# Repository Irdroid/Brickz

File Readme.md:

**Brickz Bluetooth Infrared Blaster / Transmitter by Irdroid**

**Introduction** 

Brickz is a Open Source Platform Independent Bluetooth Infrared Transmitter / Blaster that supports GNU Linux, MS Windows MAC OS X and Android. Brickz allows you to transmit Pronto HEX Infrared codes via its built-in infrared LEDs or via a IR extender cable that connect to brickz via a 3.5mm Mono Audio jack. The unit is capable of connecting to the host PC via USB as well as Bluetooth. It shows up as a bluetooth serial port, when that interface option is used, or as a USB Serial Device if the USB Interface connection is used.(https://irdroid.eu/product/brickz/)

**Features:**
- Bluetooth communication with the HOST SYSTEM / MCU
- USB Connection with the host System
- Built-in high power infrared leds
- Optional infrared transmitter extender
- Infrared operates at 940nm wavelength

**Example Application:**
- Digital signage infrared remote control & automation
- Home Automation & remote control
- Media remote control & automation systems

**How It works?**

Brickz listens for PRONTO HEX infrared codes via USB<>Serial or Bluetooht, simply connect to brickz via Bluetooth or USB open a terminal and type in the PRONTO code and hit enter, the command will be blasted through Brickz.If you are using Brickz with Android you can check out the example open source application that comes with brickz for sending pronto HEX codes. For detailed examples and usage, please refer to Brickz User's Manual, available in this repo.

On MAC OS X and GNU Linux once you pair with Brickz you can send PRONTO HEX codes directly from the console or via a bash script. This gives you the ability to make automation using script or controlling infrared devices directly from the console, from a script or scheduling infrared commands via cron. On MS Windows you can use any terminal application such as realterm or putty to send infrared commands with Brickz, or use the SerialSend.exe command line utility to send Infrared Codes to Brickz.

**Product website and Documentation**

- [Brickz official product Website](https://irdroid.eu/product/brickz)
- Documentation, Schematics, Production files and Software for Brickz can be found in this repository.

**Purchase sample unit**

- [Brickz official product Website](https://irdroid.eu/product/brickz)
- [Tindie](https://www.tindie.com/products/irdroid/brickz-bluetooth-infrared-transmitter/)

**You want to help with the development?**

- Write us an email to info@irdroid.com

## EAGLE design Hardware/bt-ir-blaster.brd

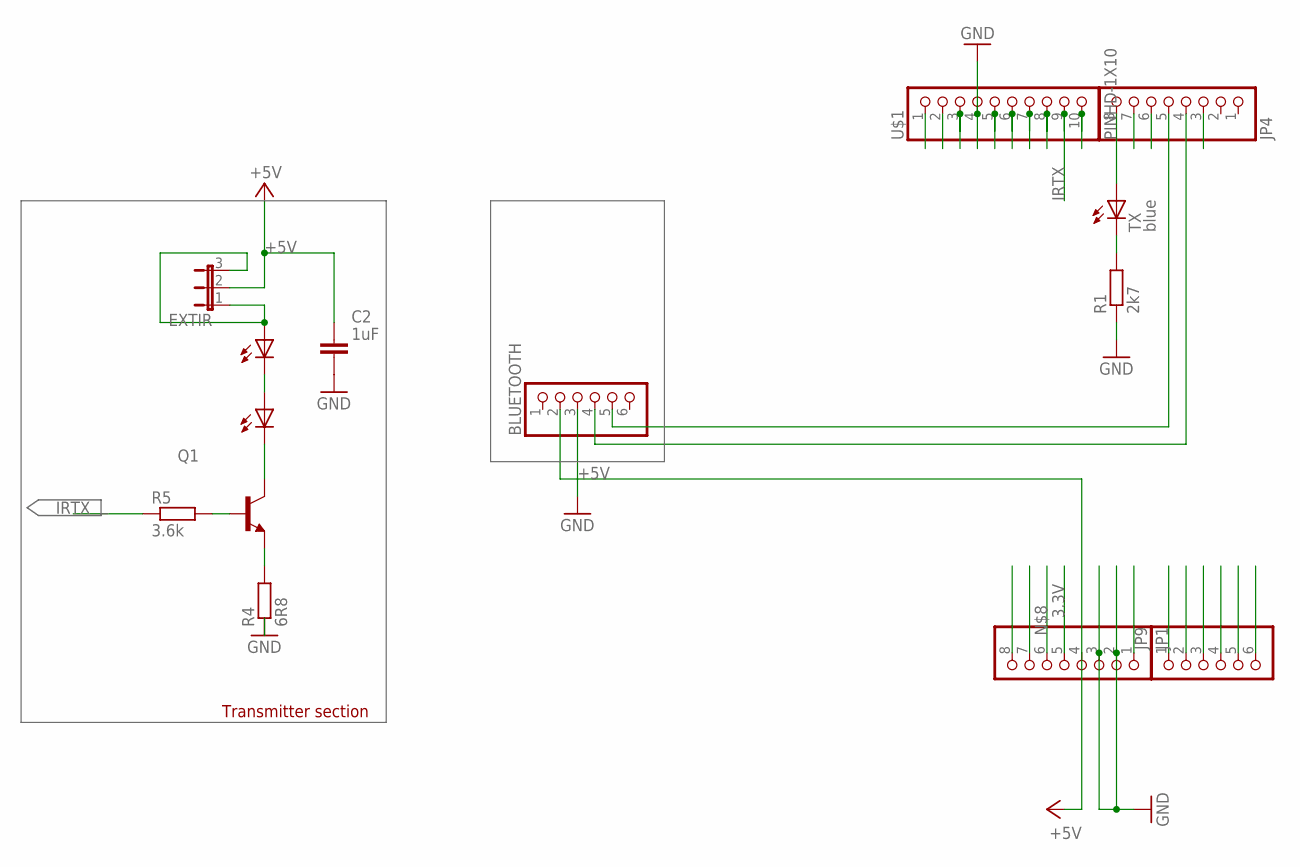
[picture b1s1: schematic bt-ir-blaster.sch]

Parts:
BLUETOOTH: PINHD-1X6; 1X06
C2: 1uF; C603@1
EXTIR: JP2E; JP2
JP1, JP4: PINHD-1X8BIG; 1X08-BIG
JP9: PINHD-1X6B; 1X06-BIG
Q1: TRANSISTOR_BJT_NPN-SOT-23-BCE; SOT-23
R1: 2k7; R0805
R4: 6R8; R1206
R5: 3.6k; R0603
TX: blue; LED3MM
U$1: PINHD-1X10; 1X10-BIG
U$5, U$7: IRLED5MM; IRLED_HOLDER

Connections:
3.3V: JP1.5
+5V: BLUETOOTH.2, C2.1, EXTIR.2, JP1.4
A: Q1.2 (C), U$5.K (C)
GND: BLUETOOTH.3, C2.2, JP1.2, JP1.3, R1.1, R4.1, U$1.4
IRTX: R5.1, U$1.9
K: Q1.3 (E), R4.2
unnamed: Q1.1 (B), R5.2
unnamed: U$5.A, U$7.K (C)
unnamed: R1.2, TX.K (C)
unnamed: EXTIR.1, EXTIR.3, U$7.A
unnamed: BLUETOOTH.4, JP4.4
unnamed: BLUETOOTH.5, JP4.5
unnamed: JP4.8, TX.A

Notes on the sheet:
Transmitter section

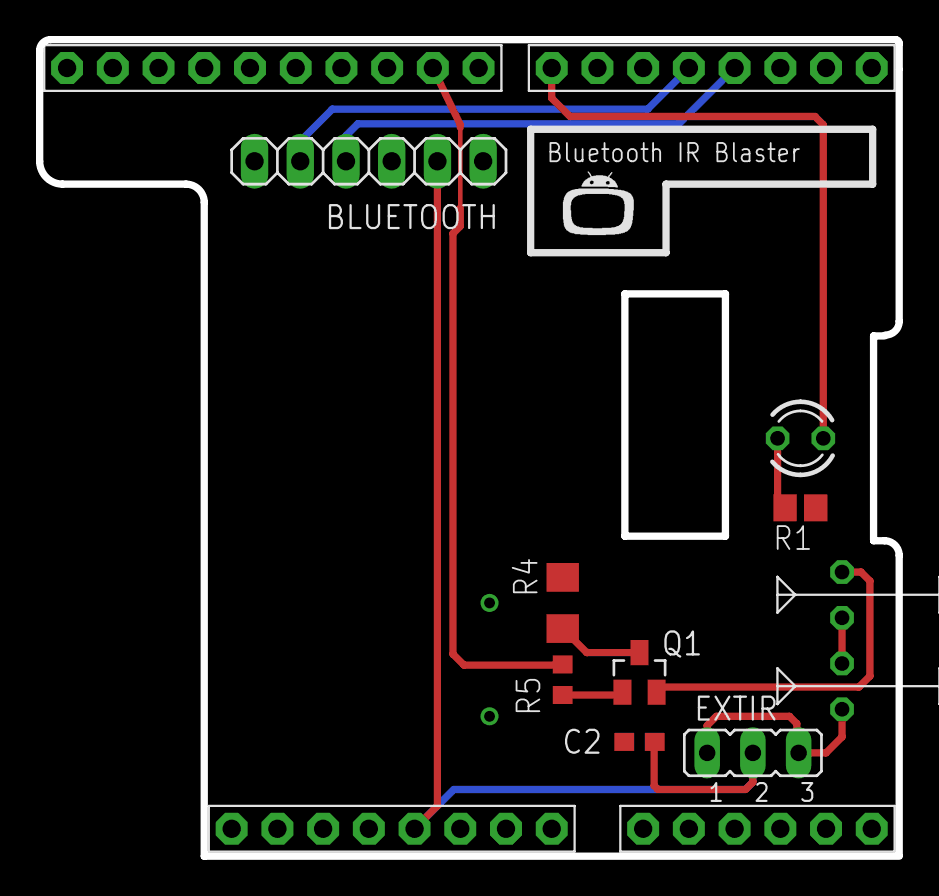
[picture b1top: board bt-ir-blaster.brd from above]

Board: 2 copper layers, 47.8 x 45.4 mm, 15 parts (0 on the bottom side), 12 nets.

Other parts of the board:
U$44: IRDROIDLOGO

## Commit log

2021-01-21 Brickz Initial commit
    Brickz Initial commit
2021-01-21 Added photos
2021-01-21 Added Readme.md
    Readme.md
2021-01-21 Readme update
